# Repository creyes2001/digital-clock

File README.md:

# DIGITAL CLOCK

## Overview

This is a bare-metal C project based on the Microchip PIC18F4550 microcontroller that implements a digital clock.
The system uses multiplexed seven-segment displays to show the current time and provides a push-button interface for user configuration.
The configured time is stored in the internal EEPROM memory.

## Features

- Modular driver-based firmware architecture
- Timer2-driven system tick for timekeeping and scheduling
- Multiplexed seven-segment display control
- Push-button interface for user configuration
- EEPROM-based non-volatile time storage

## Hardware 

- Microchip PIC18F4550 microcontroller with a 16 MHz external crystal oscillator 
- Multiplexed common-cathode seven-segment display
- NPN transistors for digit control
- Push-button interface with pull-up resistors

## Software architecture

The firmware is organized using a modular architecture that separates hardware drivers from application logic.

The modules include:

- GPIO HAL for low-level pin control
- Display driver for multiplexed seven-segment control
- Button driver for user input handling
- System tick dirver providing a 1 ms time base
- EEPROM driver for non-volatile data storage
- Clock driver for real-time management
- UART driver for testing and debugging

## How It Works?

The system operates on a 1 ms system tick generated by the Timer2 peripherial.
The tick drives a cooperative scheduler responsible for executing periodic tasks and maintaining the system time.
The scheduler manages key tasks such as button input processing, display multiplexing, and timekeeping.
This approach ensures accurate timing efficient CPU utilization.

## Challenges & Design Decisions

### Display ghosting

My initial design used common-anode displays driven by PNP transistors 
through a Darlington array, chosen to limit the current going through 
the PIC's GPIO pins. This setup caused visible ghosting: the Darlington 
array's slow switching times and high saturation voltage drop meant 
that the previous digit didn't fully turn off before the next one 
turned on during multiplexing.

I redesigned the digit-drive stage with common-cathode displays driven 
directly by NPN transistors. The faster switching produced cleaner 
digit transitions and eliminated the ghosting entirely. This taught me 
that in embedded development, firmware correctness alone isn't enough — 
the underlying circuit topology can make or break a working system.

## Build Instruction
```bash
make all
make flash
make clean
```
## Schematic

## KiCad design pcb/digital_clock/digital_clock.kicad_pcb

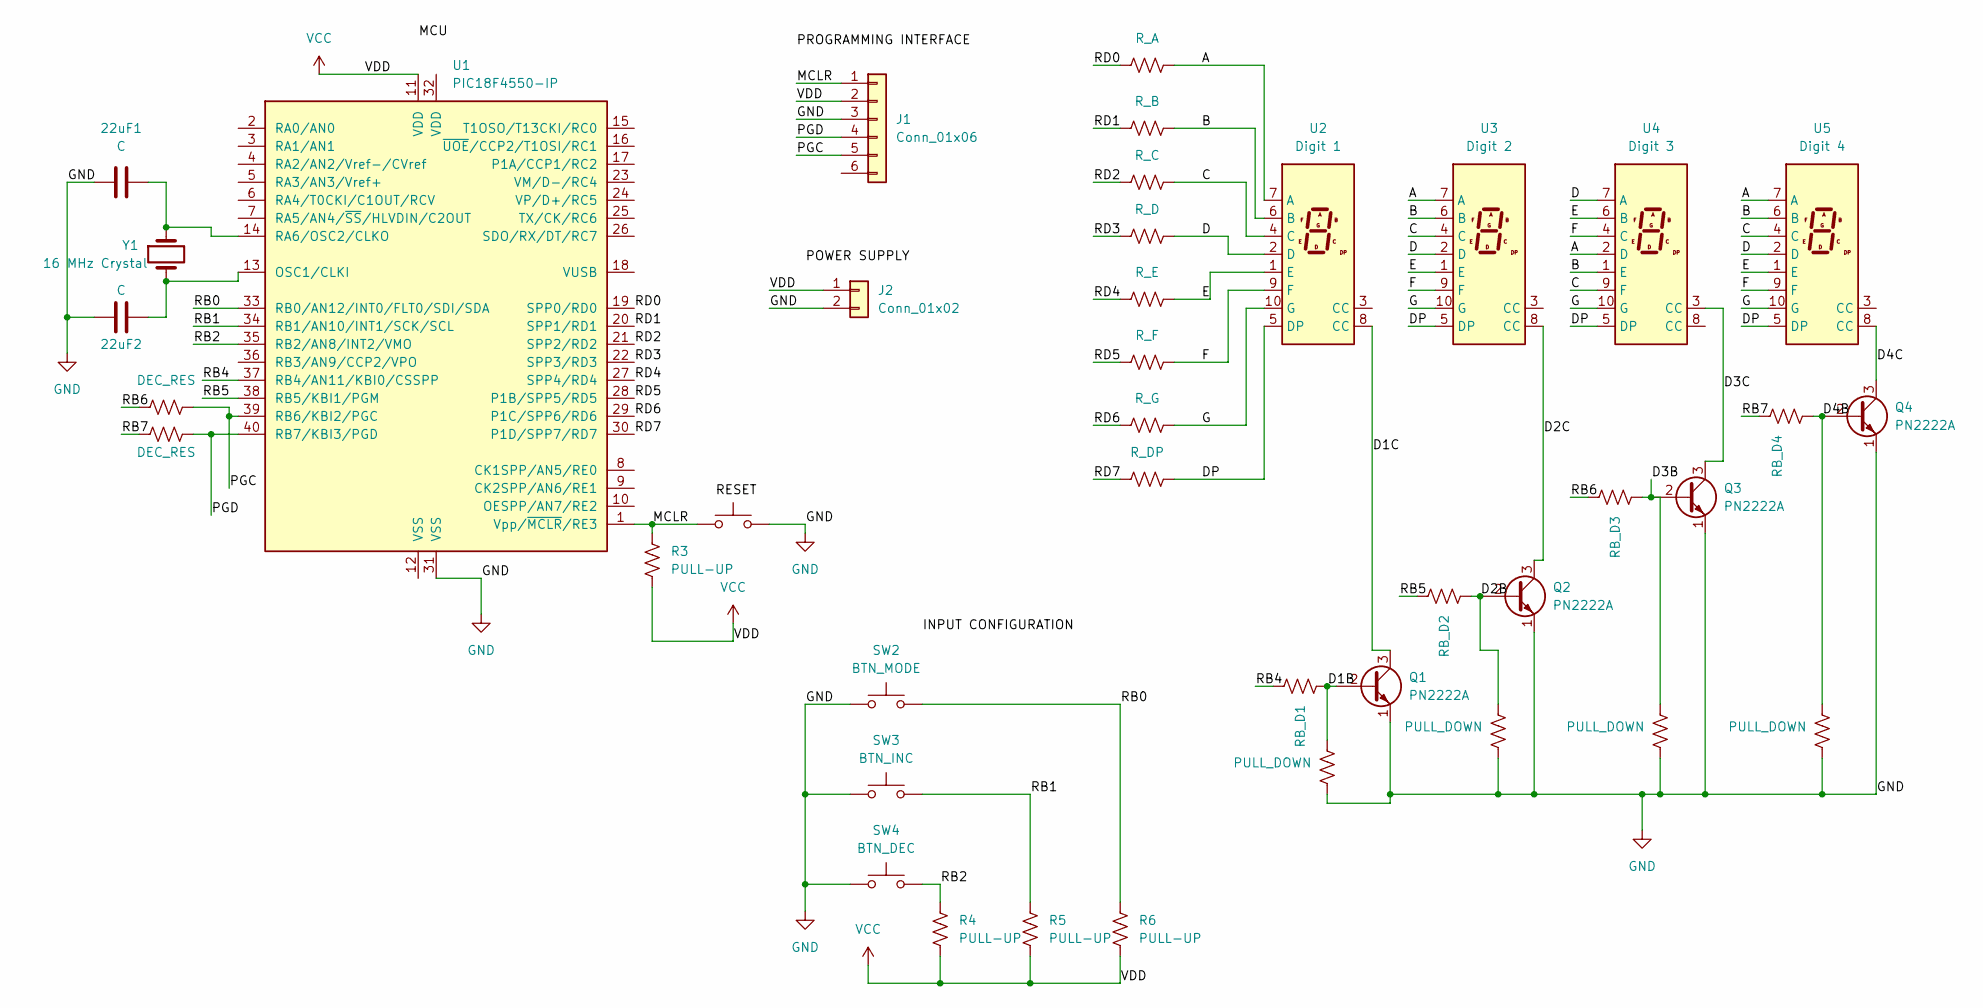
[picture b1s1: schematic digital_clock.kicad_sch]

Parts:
22uF1, 22uF2: C; C_Disc_D3.0mm_W1.6mm_P2.50mm
J1: Conn_01x06; PinHeader_1x06_P2.54mm_Horizontal
J2: Conn_01x02; PhoenixContact_MCV_1,5_2-G-5.08_1x02_P5.08mm_Vertical
Q1, Q2, Q3, Q4: PN2222A; TO-92_Inline
R1, R2: DEC_RES; R_Axial_DIN0207_L6.3mm_D2.5mm_P7.62mm_Horizontal
R3, R4, R5, R6: PULL-UP; R_Axial_DIN0207_L6.3mm_D2.5mm_P7.62mm_Horizontal
R7: R_A; R_Axial_DIN0207_L6.3mm_D2.5mm_P7.62mm_Horizontal
R8: R_B; R_Axial_DIN0207_L6.3mm_D2.5mm_P7.62mm_Horizontal
R9: R_C; R_Axial_DIN0207_L6.3mm_D2.5mm_P7.62mm_Horizontal
R10: R_D; R_Axial_DIN0207_L6.3mm_D2.5mm_P7.62mm_Horizontal
R11: R_E; R_Axial_DIN0207_L6.3mm_D2.5mm_P7.62mm_Horizontal
R12: R_F; R_Axial_DIN0207_L6.3mm_D2.5mm_P7.62mm_Horizontal
R13: R_G; R_Axial_DIN0207_L6.3mm_D2.5mm_P7.62mm_Horizontal
R14: R_DP; R_Axial_DIN0207_L6.3mm_D2.5mm_P7.62mm_Horizontal
R15: RB_D1; R_Axial_DIN0207_L6.3mm_D2.5mm_P7.62mm_Horizontal
R16, R18, R20, R22: PULL_DOWN; R_Axial_DIN0207_L6.3mm_D2.5mm_P7.62mm_Horizontal
R17: RB_D2; R_Axial_DIN0207_L6.3mm_D2.5mm_P7.62mm_Horizontal
R19: RB_D3; R_Axial_DIN0207_L6.3mm_D2.5mm_P7.62mm_Horizontal
R21: RB_D4; R_Axial_DIN0207_L6.3mm_D2.5mm_P7.62mm_Horizontal
SW1: SW_Push; SW_PUSH_6mm
SW2: BTN_MODE; SW_PUSH_6mm
SW3: BTN_INC; SW_PUSH_6mm
SW4: BTN_DEC; SW_PUSH_6mm
U1: PIC18F4550-IP; DIP-40_W15.24mm
U2: Digit 1; D1X8K
U3: Digit 2; D1X8K
U4: Digit 3; D1X8K
U5: Digit 4; D1X8K
Y1: 16 MHz Crystal; Crystal_HC49-4H_Vertical

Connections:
/A: R7.1, U2.7 (A), U3.7 (A), U4.2 (D), U5.7 (A)
/B: R8.1, U2.6 (B), U3.6 (B), U4.1 (E), U5.6 (B)
/C: R9.1, U2.4 (C), U3.4 (C), U4.9 (F), U5.4 (C)
/D: R10.1, U2.2 (D), U3.2 (D), U4.7 (A), U5.2 (D)
/D1B: Q1.2 (B), R15.1, R16.2
/D1C: Q1.3 (C), U2.8 (CC)
/D2B: Q2.2 (B), R17.1, R18.2
/D2C: Q2.3 (C), U3.8 (CC)
/D3B: Q3.2 (B), R19.1, R20.2
/D3C: Q3.3 (C), U4.3 (CC)
/D4B: Q4.2 (B), R21.1, R22.2
/D4C: Q4.3 (C), U5.8 (CC)
/DP: R14.1, U2.5 (DP), U3.5 (DP), U4.5 (DP), U5.5 (DP)
/E: R11.1, U2.1 (E), U3.1 (E), U4.6 (B), U5.1 (E)
/F: R12.1, U2.9 (F), U3.9 (F), U4.4 (C), U5.9 (F)
/G: R13.1, U2.10 (G), U3.10 (G), U4.10 (G), U5.10 (G)
/MCLR: J1.1, R3.1, SW1.1, U1.1 (Vpp/~MCLR/RE3)
/PGC: J1.5, R1.1, U1.39 (RB6/KBI2/PGC)
/PGD: J1.4, R2.1, U1.40 (RB7/KBI3/PGD)
/RB0: R6.1, SW2.2, U1.33 (RB0/AN12/INT0/FLT0/SDI/SDA)
/RB1: R5.1, SW3.2, U1.34 (RB1/AN10/INT1/SCK/SCL)
/RB2: R4.1, SW4.2, U1.35 (RB2/AN8/INT2/VMO)
/RB4: R15.2, U1.37 (RB4/AN11/KBI0/CSSPP)
/RB5: R17.2, U1.38 (RB5/KBI1/PGM)
/RB6: R1.2, R19.2
/RB7: R2.2, R21.2
/RD0: R7.2, U1.19 (SPP0/RD0)
/RD1: R8.2, U1.20 (SPP1/RD1)
/RD2: R9.2, U1.21 (SPP2/RD2)
/RD3: R10.2, U1.22 (SPP3/RD3)
/RD4: R11.2, U1.27 (SPP4/RD4)
/RD5: R12.2, U1.28 (P1B/SPP5/RD5)
/RD6: R13.2, U1.29 (P1C/SPP6/RD6)
/RD7: R14.2, U1.30 (P1D/SPP7/RD7)
GND: 22uF1.2, 22uF2.2, J1.3, J2.2, Q1.1 (E), Q2.1 (E), Q3.1 (E), Q4.1 (E), R16.1, R18.1, R20.1, R22.1, SW1.2, SW2.1, SW3.1, SW4.1, U1.31 (VSS)
unnamed: 22uF2.1, U1.13 (OSC1/CLKI), Y1.2
unnamed: 22uF1.1, U1.14 (RA6/OSC2/CLKO), Y1.1
VCC: J1.2, J2.1, R3.2, R4.2, R5.2, R6.2, U1.11 (VDD)

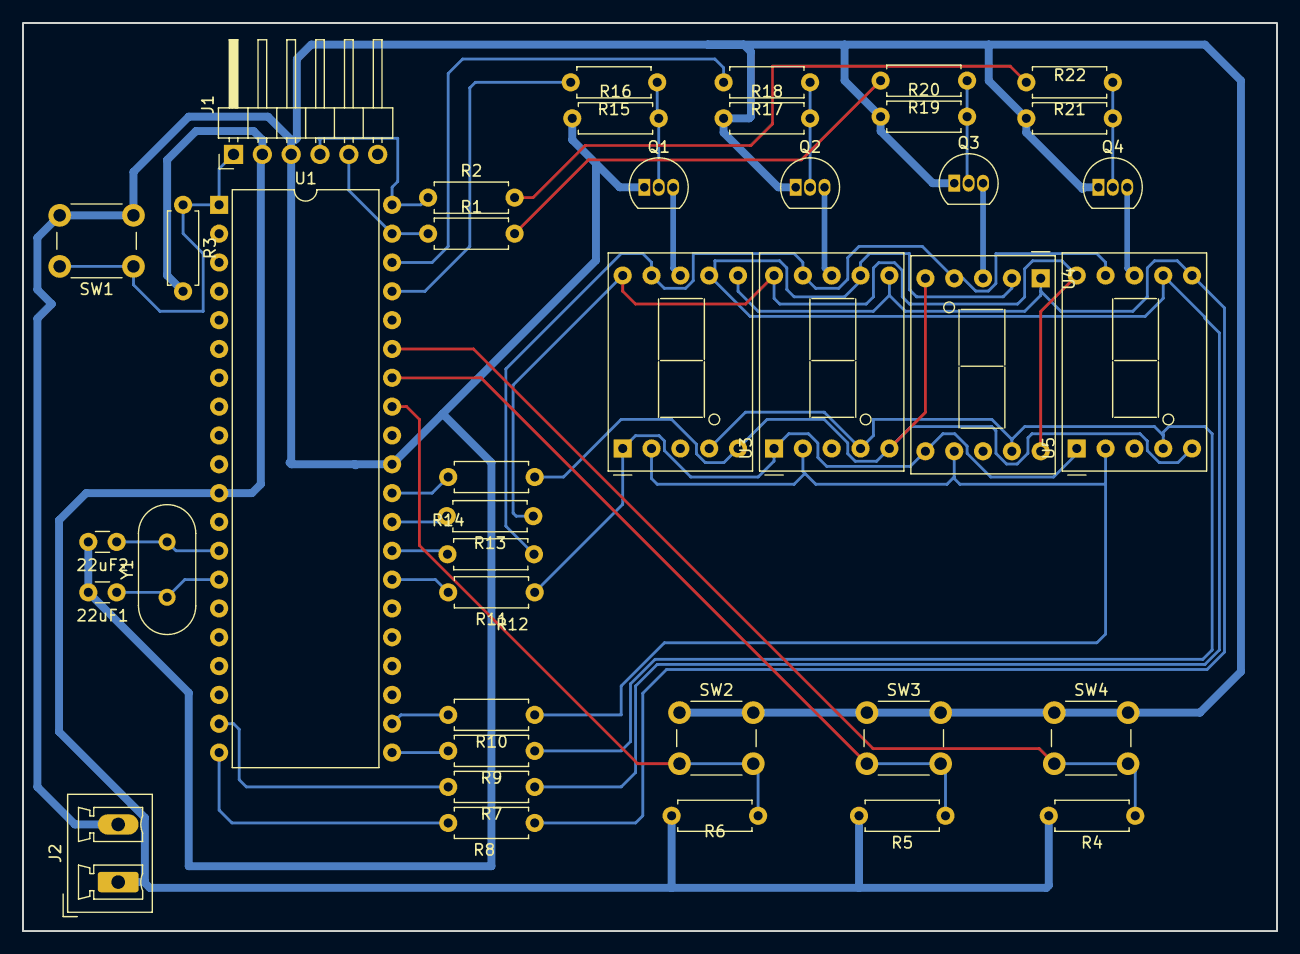
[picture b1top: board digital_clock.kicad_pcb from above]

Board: 2 copper layers, 110.5 x 80.0 mm, 40 parts (0 on the bottom side), 38 nets.

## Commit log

2026-01-29 Add clock skeleton
2026-01-29 Add gpio driver skeleton
2026-01-29 Add GPIO dirver logic and test
2026-01-29 Add Ring Buffer skeleton and logic
2026-01-30 Fix buffer bugs
2026-01-30 Fix Buffer data type
2026-01-31 Add UART driver skeleton
2026-01-31 Add Uart driver improvements and logic
2026-01-31 Fix: Define gpio structs pinters inside the uart structure
2026-02-05 feat: implemented TXIF polling for UART transmission
2026-02-12 Implement UART transmission and reception using ring buffers
2026-02-13 Implement interrupt-driven reception
2026-02-14 Implemented Uart interrupt-driven transmission
2026-02-16 Add external printf implementation for embedded systems
2026-02-16 Included and tested the external printf implementation
2026-02-16 Include timer 0 driver files from past projects
2026-02-17 Add interrupt module to centralize ISR dispatching and global interrupt initialization
2026-02-17 Add system tick module to aggregate 1 ms ticks and generate 1 s event
2026-02-17 Implement clock module using the 1 second base time provied by system tick
2026-02-17 feat: integrate debounced button driver with system tick
2026-02-26 feat: Add seven segment display module
2026-03-10 feat: Add seven segment implementation and time provided by the clock module
2026-03-11 feat: Add data EEPROM module implementation
2026-03-11 feat: Add clock storage module
2026-03-11 feat: Add colon blink function inside the display driver
2026-03-13 Fix: reduce ghosting during display multiplexing
2026-03-24 fix: improve system time base accuracy with Timer 2 driver
2026-03-24 Docs: Add README documentation
2026-03-24 Docs: Add README.md documentation
2026-03-24 Add: docs structure
2026-04-01 Docs: add schematic image
2026-04-01 Fix: schematic image path
2026-04-27 Add: .gitignore
2026-04-27 Add: .gitattributes
2026-04-27 Fix linguist: use recursive glob for build and external dirs
2026-04-27 docs(readme): add Challenges & Design Decisions section
